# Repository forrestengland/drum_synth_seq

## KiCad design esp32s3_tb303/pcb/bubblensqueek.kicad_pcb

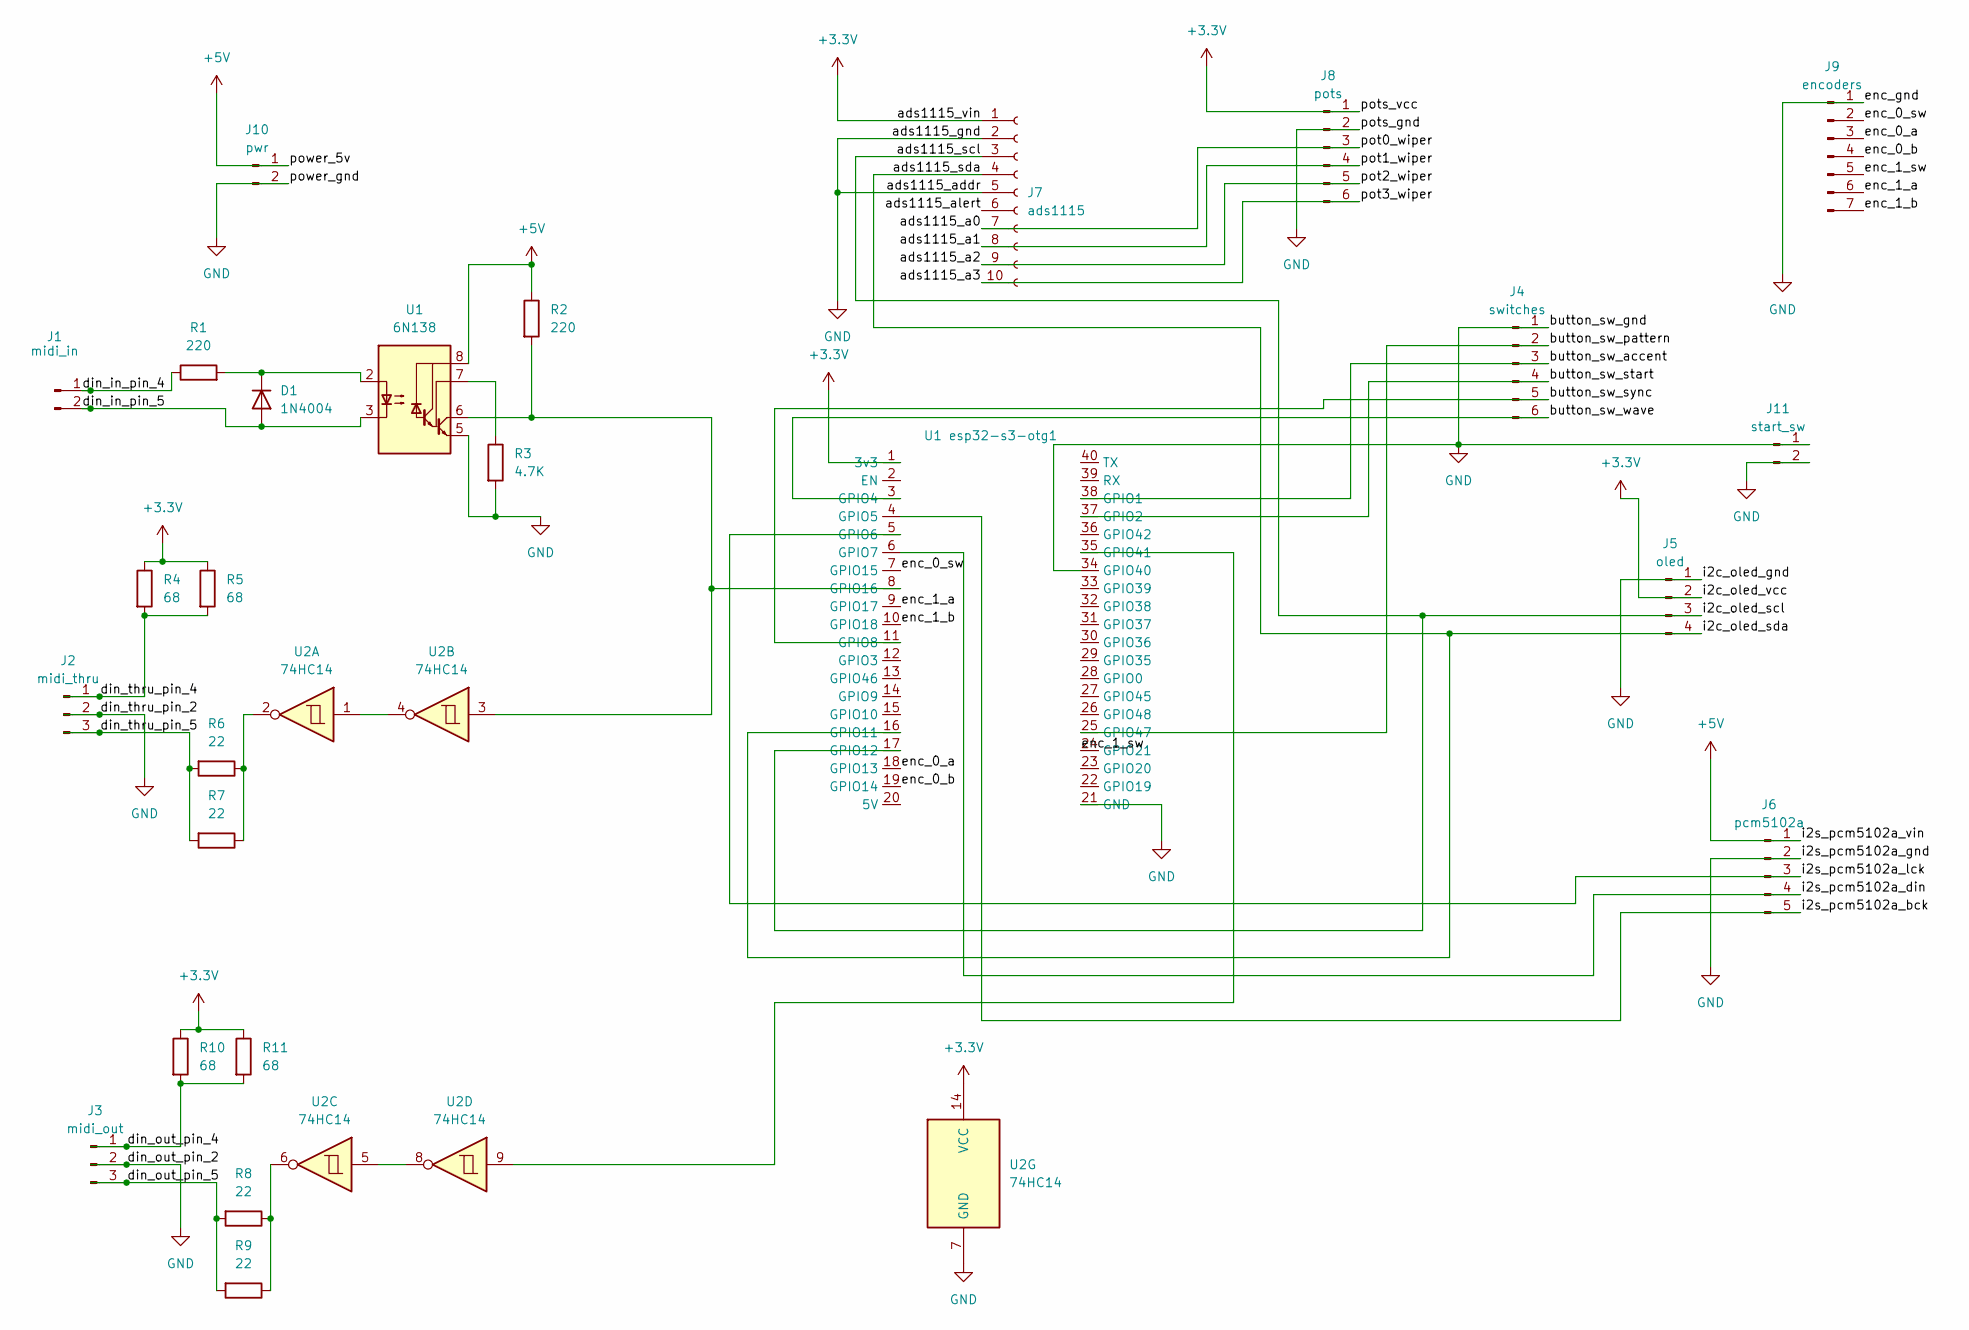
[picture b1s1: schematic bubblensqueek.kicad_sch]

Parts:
D1: 1N4004; D_DO-41_SOD81_P10.16mm_Horizontal
J1: midi_in; PinHeader_1x02_P2.54mm_Vertical
J2: midi_thru; PinHeader_1x03_P2.54mm_Vertical
J3: midi_out; PinHeader_1x03_P2.54mm_Vertical
J4: switches; PinHeader_1x06_P2.54mm_Vertical
J5: oled; PinHeader_1x04_P2.54mm_Vertical
J6: pcm5102a; PinHeader_1x05_P2.54mm_Vertical
J7: ads1115; PinHeader_1x10_P2.54mm_Vertical
J8: pots; PinHeader_1x06_P2.54mm_Vertical
J9: encoders; PinHeader_1x07_P2.54mm_Vertical
J10: pwr; PinHeader_1x02_P2.54mm_Vertical
J11: start_sw; PinHeader_1x02_P2.54mm_Vertical
R1, R2: 220; R_Axial_DIN0207_L6.3mm_D2.5mm_P7.62mm_Horizontal
R3: 4.7K; R_Axial_DIN0207_L6.3mm_D2.5mm_P7.62mm_Horizontal
R4, R5, R10, R11: 68; R_Axial_DIN0207_L6.3mm_D2.5mm_P7.62mm_Horizontal
R6, R7, R8, R9: 22; R_Axial_DIN0207_L6.3mm_D2.5mm_P7.62mm_Horizontal
U1: 6N138; CERDIP-8_W7.62mm_SideBrazed_Socket
U1 esp32-s3-otg1: freenove_esp32_s3_otg
U2: 74HC14; CERDIP-14_W7.62mm_SideBrazed

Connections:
+3.3V: J5.2, J7.1, J8.1, R4.1, R5.1, R10.1, R11.1, U1 esp32-s3-otg1.1 (3v3), U2.14 (VCC)
+5V: J6.1, J10.1, R2.1, U1.8 (VCC)
/ads1115_a0: J7.7, J8.3
/ads1115_a1: J7.8, J8.4
/ads1115_a2: J7.9, J8.5
/ads1115_a3: J7.10, J8.6
/ads1115_alert: J7.6
/ads1115_scl: J5.3, J7.3, U1 esp32-s3-otg1.17 (GPIO12)
/ads1115_sda: J5.4, J7.4, U1 esp32-s3-otg1.16 (GPIO11)
/button_sw_accent: J4.3, U1 esp32-s3-otg1.38 (GPIO1)
/button_sw_pattern: J4.2, U1 esp32-s3-otg1.25 (GPIO47)
/button_sw_start: J4.4, U1 esp32-s3-otg1.37 (GPIO2)
/button_sw_sync: J4.5, U1 esp32-s3-otg1.11 (GPIO8)
/button_sw_wave: J4.6, U1 esp32-s3-otg1.3 (GPIO4)
/din_in_pin_4: J1.1, R1.1
/din_in_pin_5: D1.2 (A), J1.2, U1.3 (C2)
/din_out_pin_4: J3.1, R10.2, R11.2
/din_out_pin_5: J3.3, R8.2, R9.2
/din_thru_pin_4: J2.1, R4.2, R5.2
/din_thru_pin_5: J2.3, R6.2, R7.2
/enc_0_a: J9.3, U1 esp32-s3-otg1.18 (GPIO13)
/enc_0_b: J9.4, U1 esp32-s3-otg1.19 (GPIO14)
/enc_0_sw: J9.2, U1 esp32-s3-otg1.7 (GPIO15)
/enc_1_a: J9.6, U1 esp32-s3-otg1.9 (GPIO17)
/enc_1_b: J9.7, U1 esp32-s3-otg1.10 (GPIO18)
/enc_1_sw: J9.5, U1 esp32-s3-otg1.24 (GPIO21)
/i2s_pcm5102a_bck: J6.5, U1 esp32-s3-otg1.4 (GPIO5)
/i2s_pcm5102a_din: J6.4, U1 esp32-s3-otg1.6 (GPIO7)
/i2s_pcm5102a_lck: J6.3, U1 esp32-s3-otg1.5 (GPIO6)
GND: J2.2, J3.2, J4.1, J5.1, J6.2, J7.2, J7.5, J8.2, J9.1, J10.2, J11.1, J11.2, R3.2, U1.5 (GND), U1 esp32-s3-otg1.21 (GND), U1 esp32-s3-otg1.34 (GPIO40), U2.7 (GND)
unnamed: D1.1 (K), R1.2, U1.2 (C1)
unnamed: R6.1, R7.1, U2.2
unnamed: R8.1, R9.1, U2.6
unnamed: R2.2, U1.6 (VO2), U1 esp32-s3-otg1.8 (GPIO16), U2.3
unnamed: U1 esp32-s3-otg1.35 (GPIO41), U2.9
unnamed: R3.1, U1.7 (VO1)
unnamed: U2.1, U2.4
unnamed: U2.5, U2.8

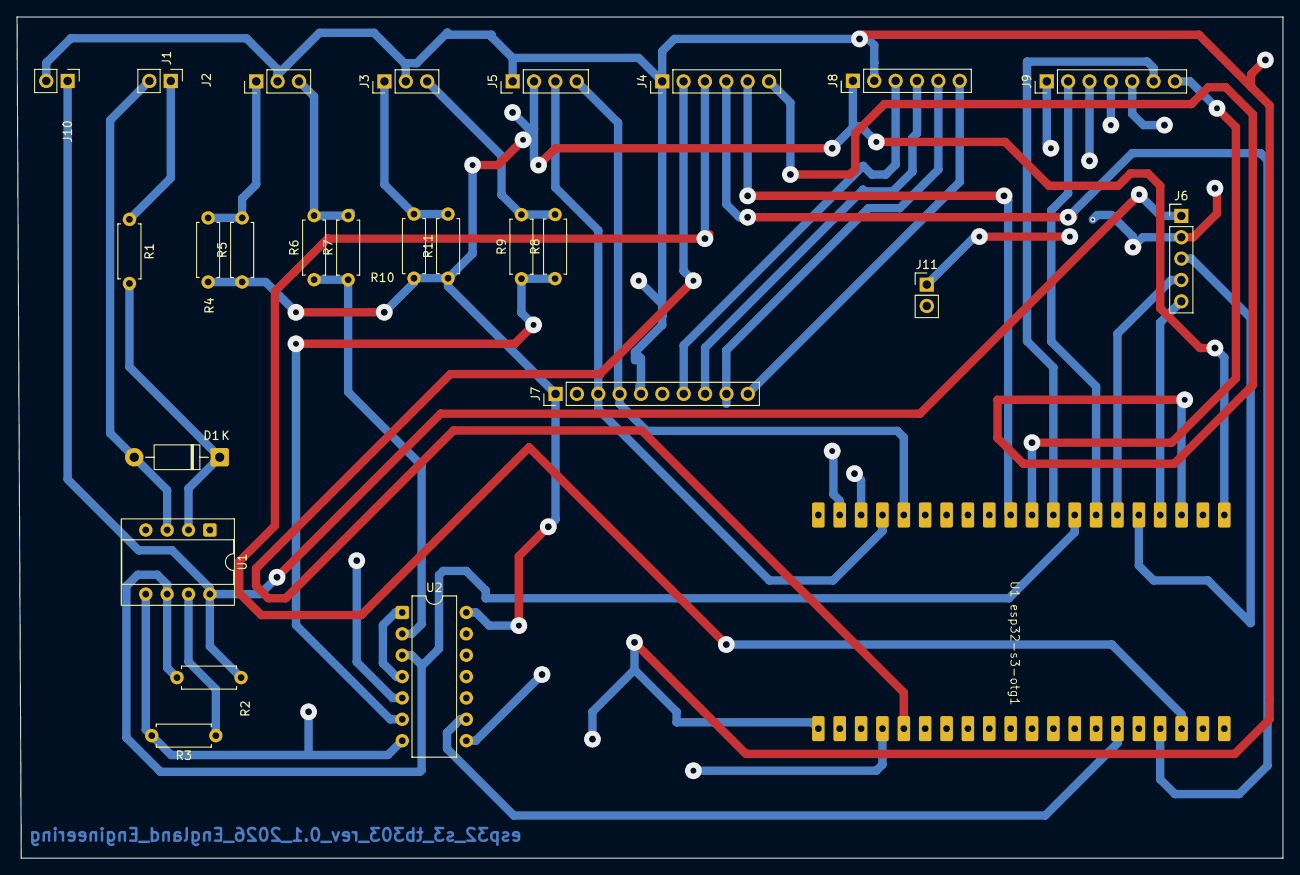
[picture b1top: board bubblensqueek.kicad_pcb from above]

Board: 2 copper layers, 150.5 x 100.0 mm, 26 parts (0 on the bottom side), 37 nets.
